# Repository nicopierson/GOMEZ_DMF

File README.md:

# GOMEZ_DMF
digital microfluidics project at CSULA

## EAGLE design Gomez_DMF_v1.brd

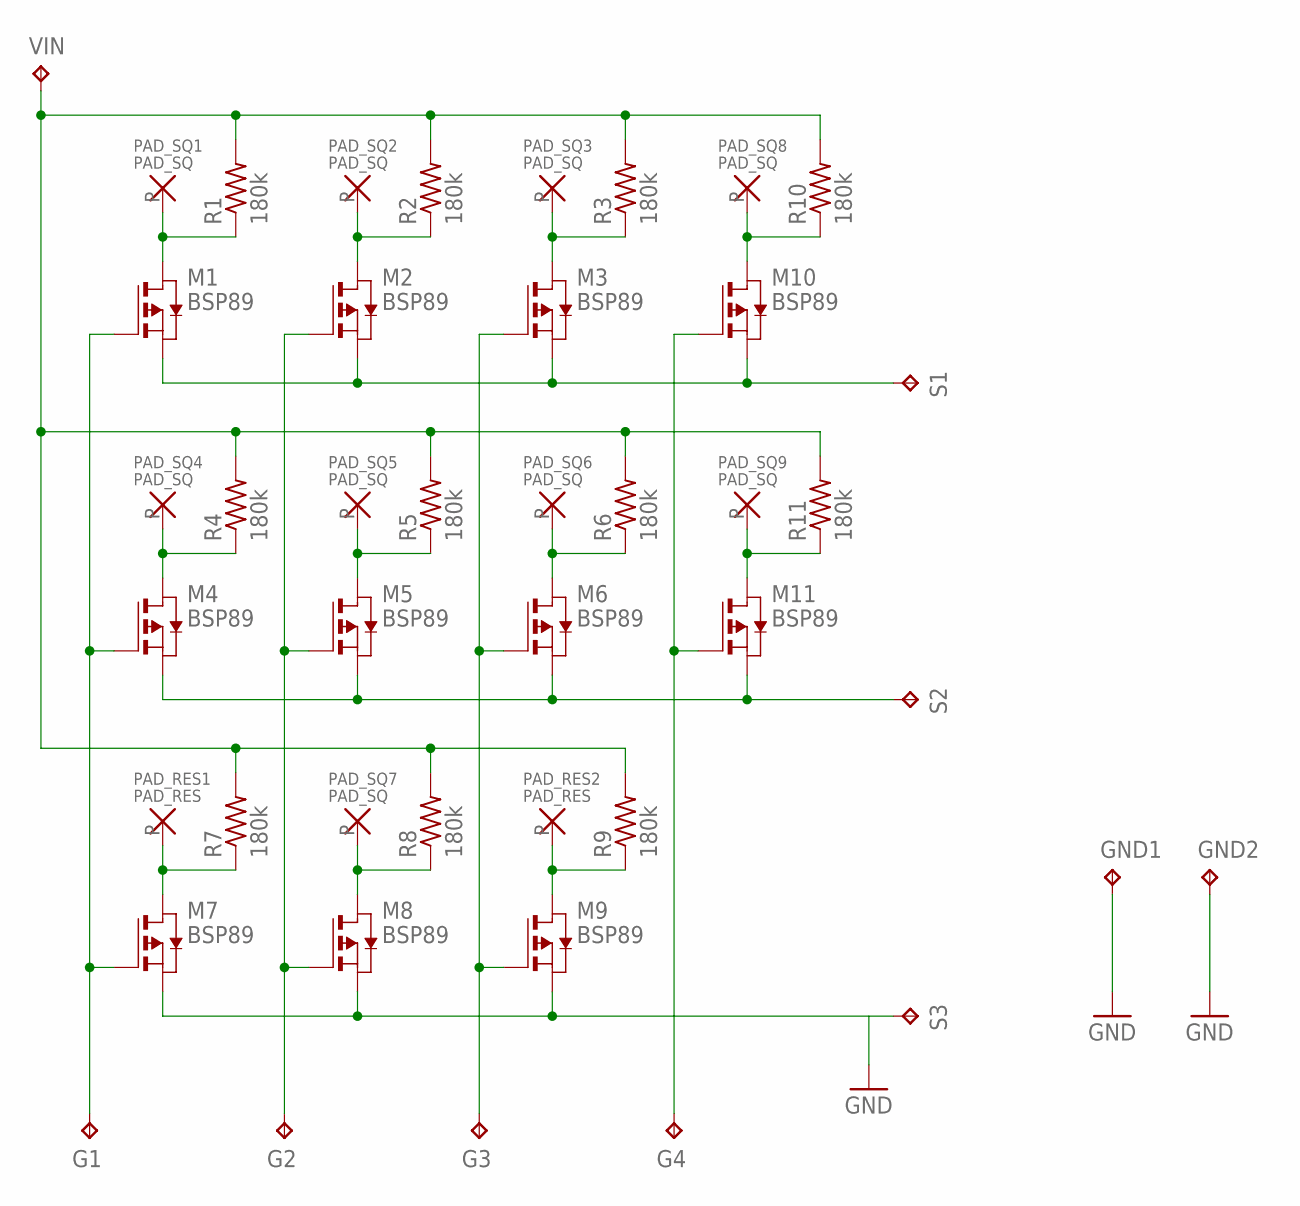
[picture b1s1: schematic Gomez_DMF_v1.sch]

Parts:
G1, G2, G3, G4: TPB2,54; B2,54
GND1, GND2: TPB2,54; B2,54
M1, M2, M3, M4, M5, M6, M7, M8, M9, M10, M11: BSP89; SOT223
PAD_RES1, PAD_RES2: PAD_RES
PAD_SQ1, PAD_SQ2, PAD_SQ3, PAD_SQ4, PAD_SQ5, PAD_SQ6, PAD_SQ7, PAD_SQ8, PAD_SQ9: PAD_SQ
R1, R2, R3, R4, R5, R6, R7, R8, R9, R10, R11: 180k; V234/12
S1, S2, S3: TPB2,54; B2,54
VIN: TPB2,54; B2,54

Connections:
GND: GND1.TP, GND2.TP
unnamed: R1.2, R2.2, R3.2, R4.2, R5.2, R6.2, R7.2, R8.2, R9.2, R10.2, R11.2, VIN.TP
unnamed: M7.2 (D), M7.4 (D), PAD_RES1.P, R7.1
unnamed: M8.2 (D), M8.4 (D), PAD_SQ7.P, R8.1
unnamed: M9.2 (D), M9.4 (D), PAD_RES2.P, R9.1
unnamed: M1.2 (D), M1.4 (D), PAD_SQ1.P, R1.1
unnamed: M2.2 (D), M2.4 (D), PAD_SQ2.P, R2.1
unnamed: M3.2 (D), M3.4 (D), PAD_SQ3.P, R3.1
unnamed: M4.2 (D), M4.4 (D), PAD_SQ4.P, R4.1
unnamed: M5.2 (D), M5.4 (D), PAD_SQ5.P, R5.1
unnamed: M6.2 (D), M6.4 (D), PAD_SQ6.P, R6.1
unnamed: M10.2 (D), M10.4 (D), PAD_SQ8.P, R10.1
unnamed: M11.2 (D), M11.4 (D), PAD_SQ9.P, R11.1
unnamed: M4.3 (S), M5.3 (S), M6.3 (S), M11.3 (S), S2.TP
unnamed: M1.3 (S), M2.3 (S), M3.3 (S), M10.3 (S), S1.TP
unnamed: G1.TP, M1.1 (G), M4.1 (G), M7.1 (G)
unnamed: G2.TP, M2.1 (G), M5.1 (G), M8.1 (G)
unnamed: G3.TP, M3.1 (G), M6.1 (G), M9.1 (G)
unnamed: M7.3 (S), M8.3 (S), M9.3 (S), S3.TP
unnamed: G4.TP, M10.1 (G), M11.1 (G)

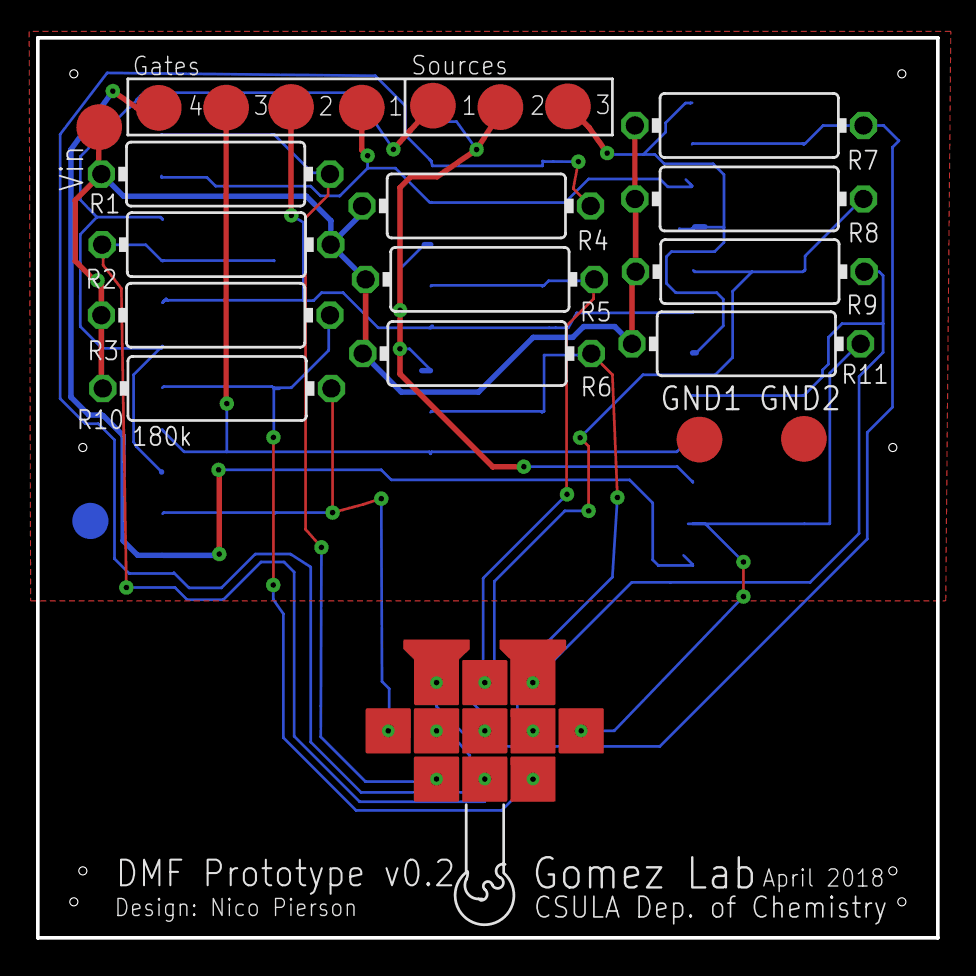
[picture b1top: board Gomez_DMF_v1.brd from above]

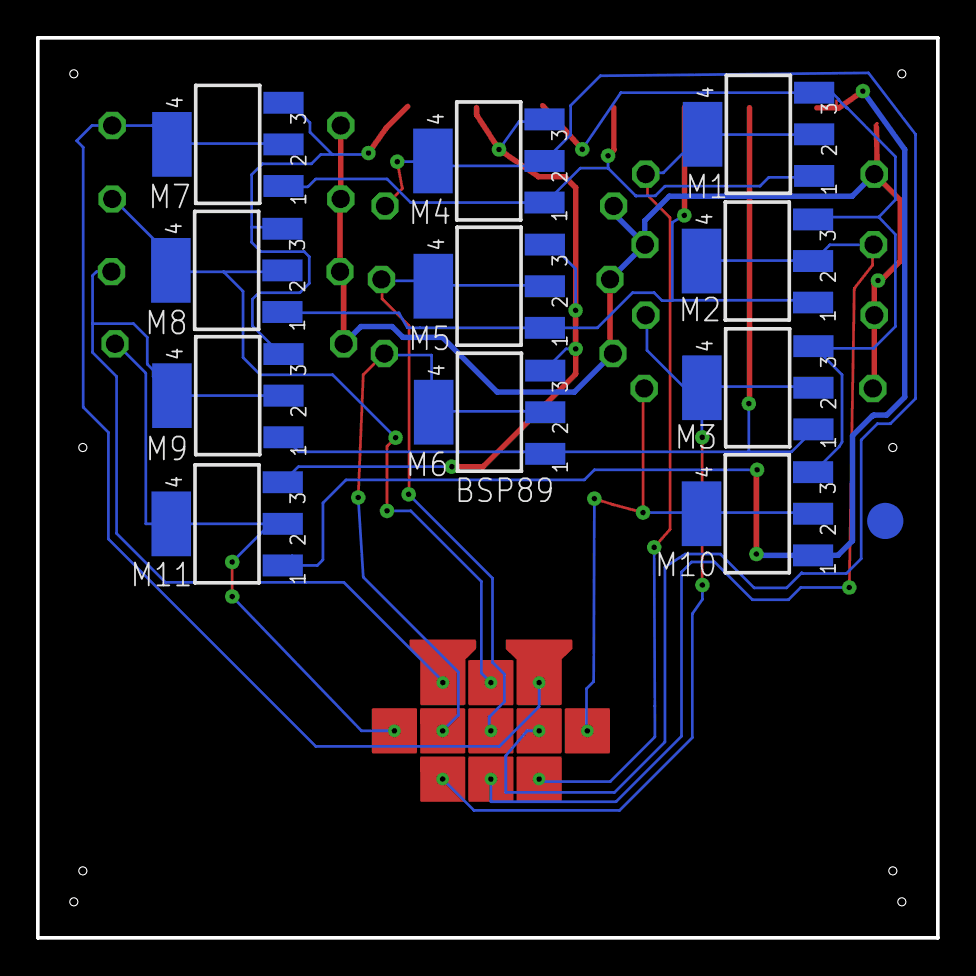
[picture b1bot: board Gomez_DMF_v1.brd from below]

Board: 2 copper layers, 50.0 x 50.0 mm, 43 parts (11 on the bottom side), 20 nets.

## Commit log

2018-05-25 favorites.txt
    websites and resources for the DMF project
2018-05-25 video of ewod
2018-05-25 cam file for 2 layer prototype board
2018-05-25 Gerber files DMF v1
2018-05-25 Arduino test code for the DMF circuit board.
